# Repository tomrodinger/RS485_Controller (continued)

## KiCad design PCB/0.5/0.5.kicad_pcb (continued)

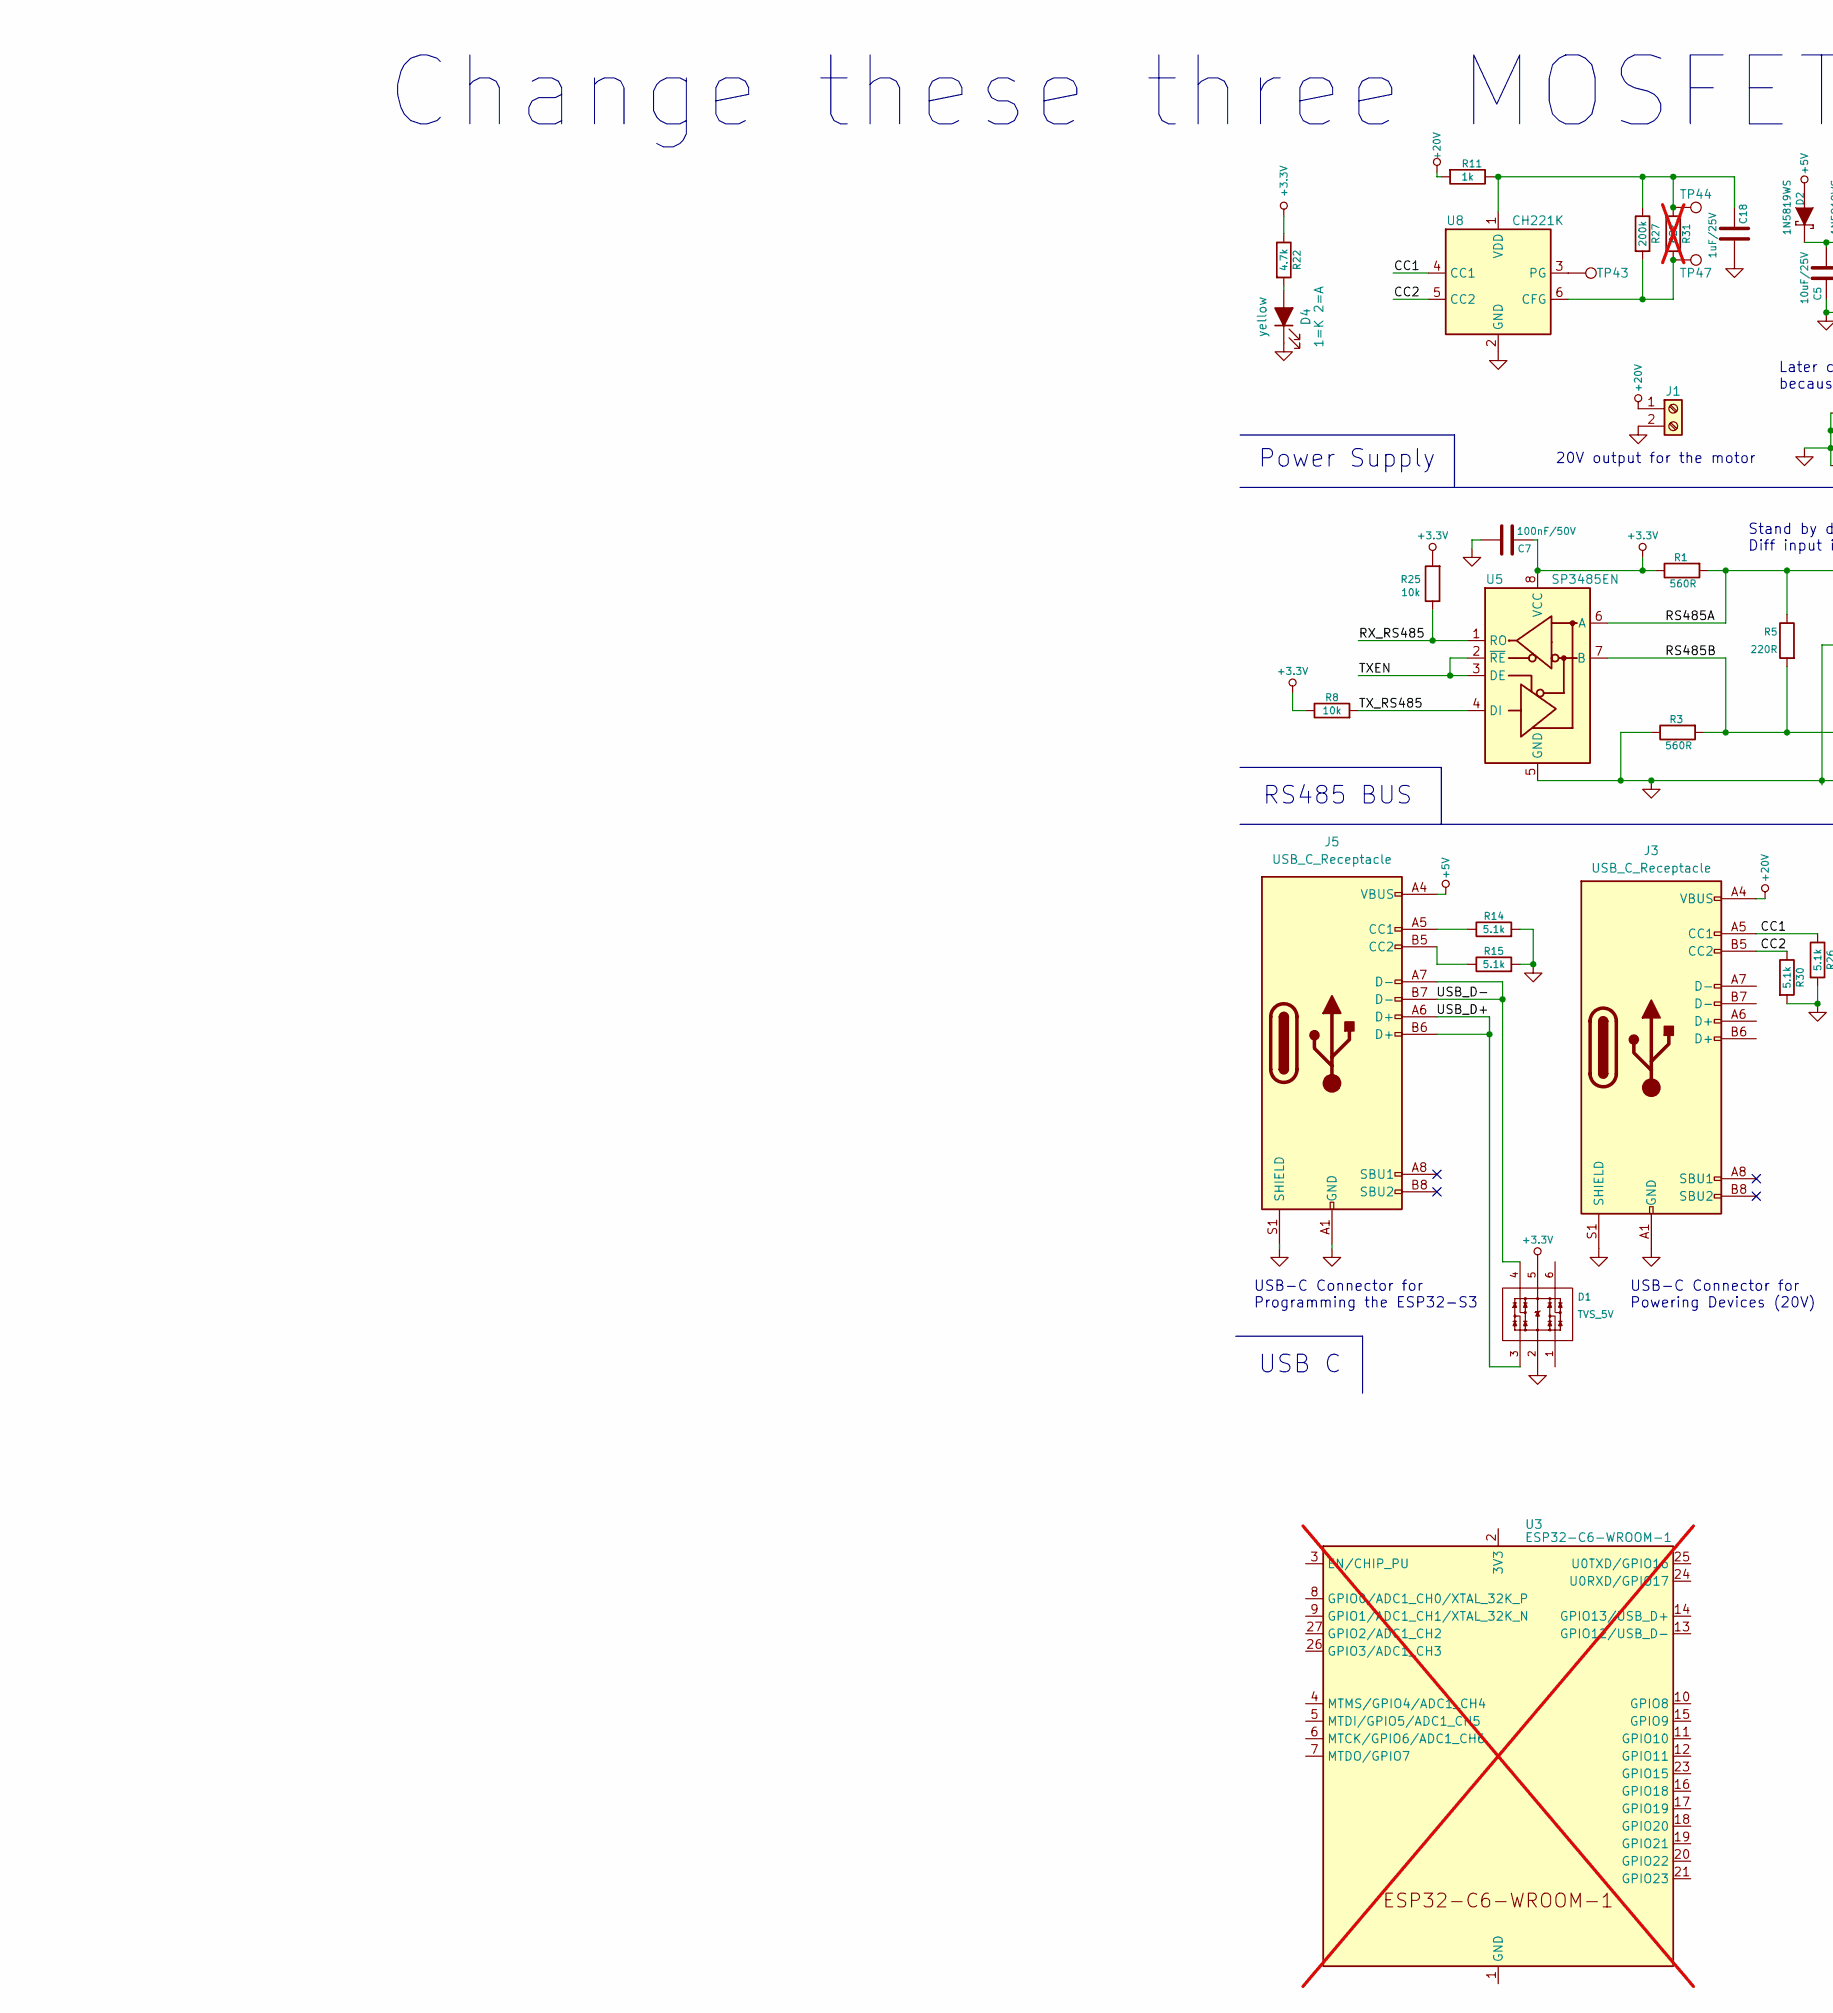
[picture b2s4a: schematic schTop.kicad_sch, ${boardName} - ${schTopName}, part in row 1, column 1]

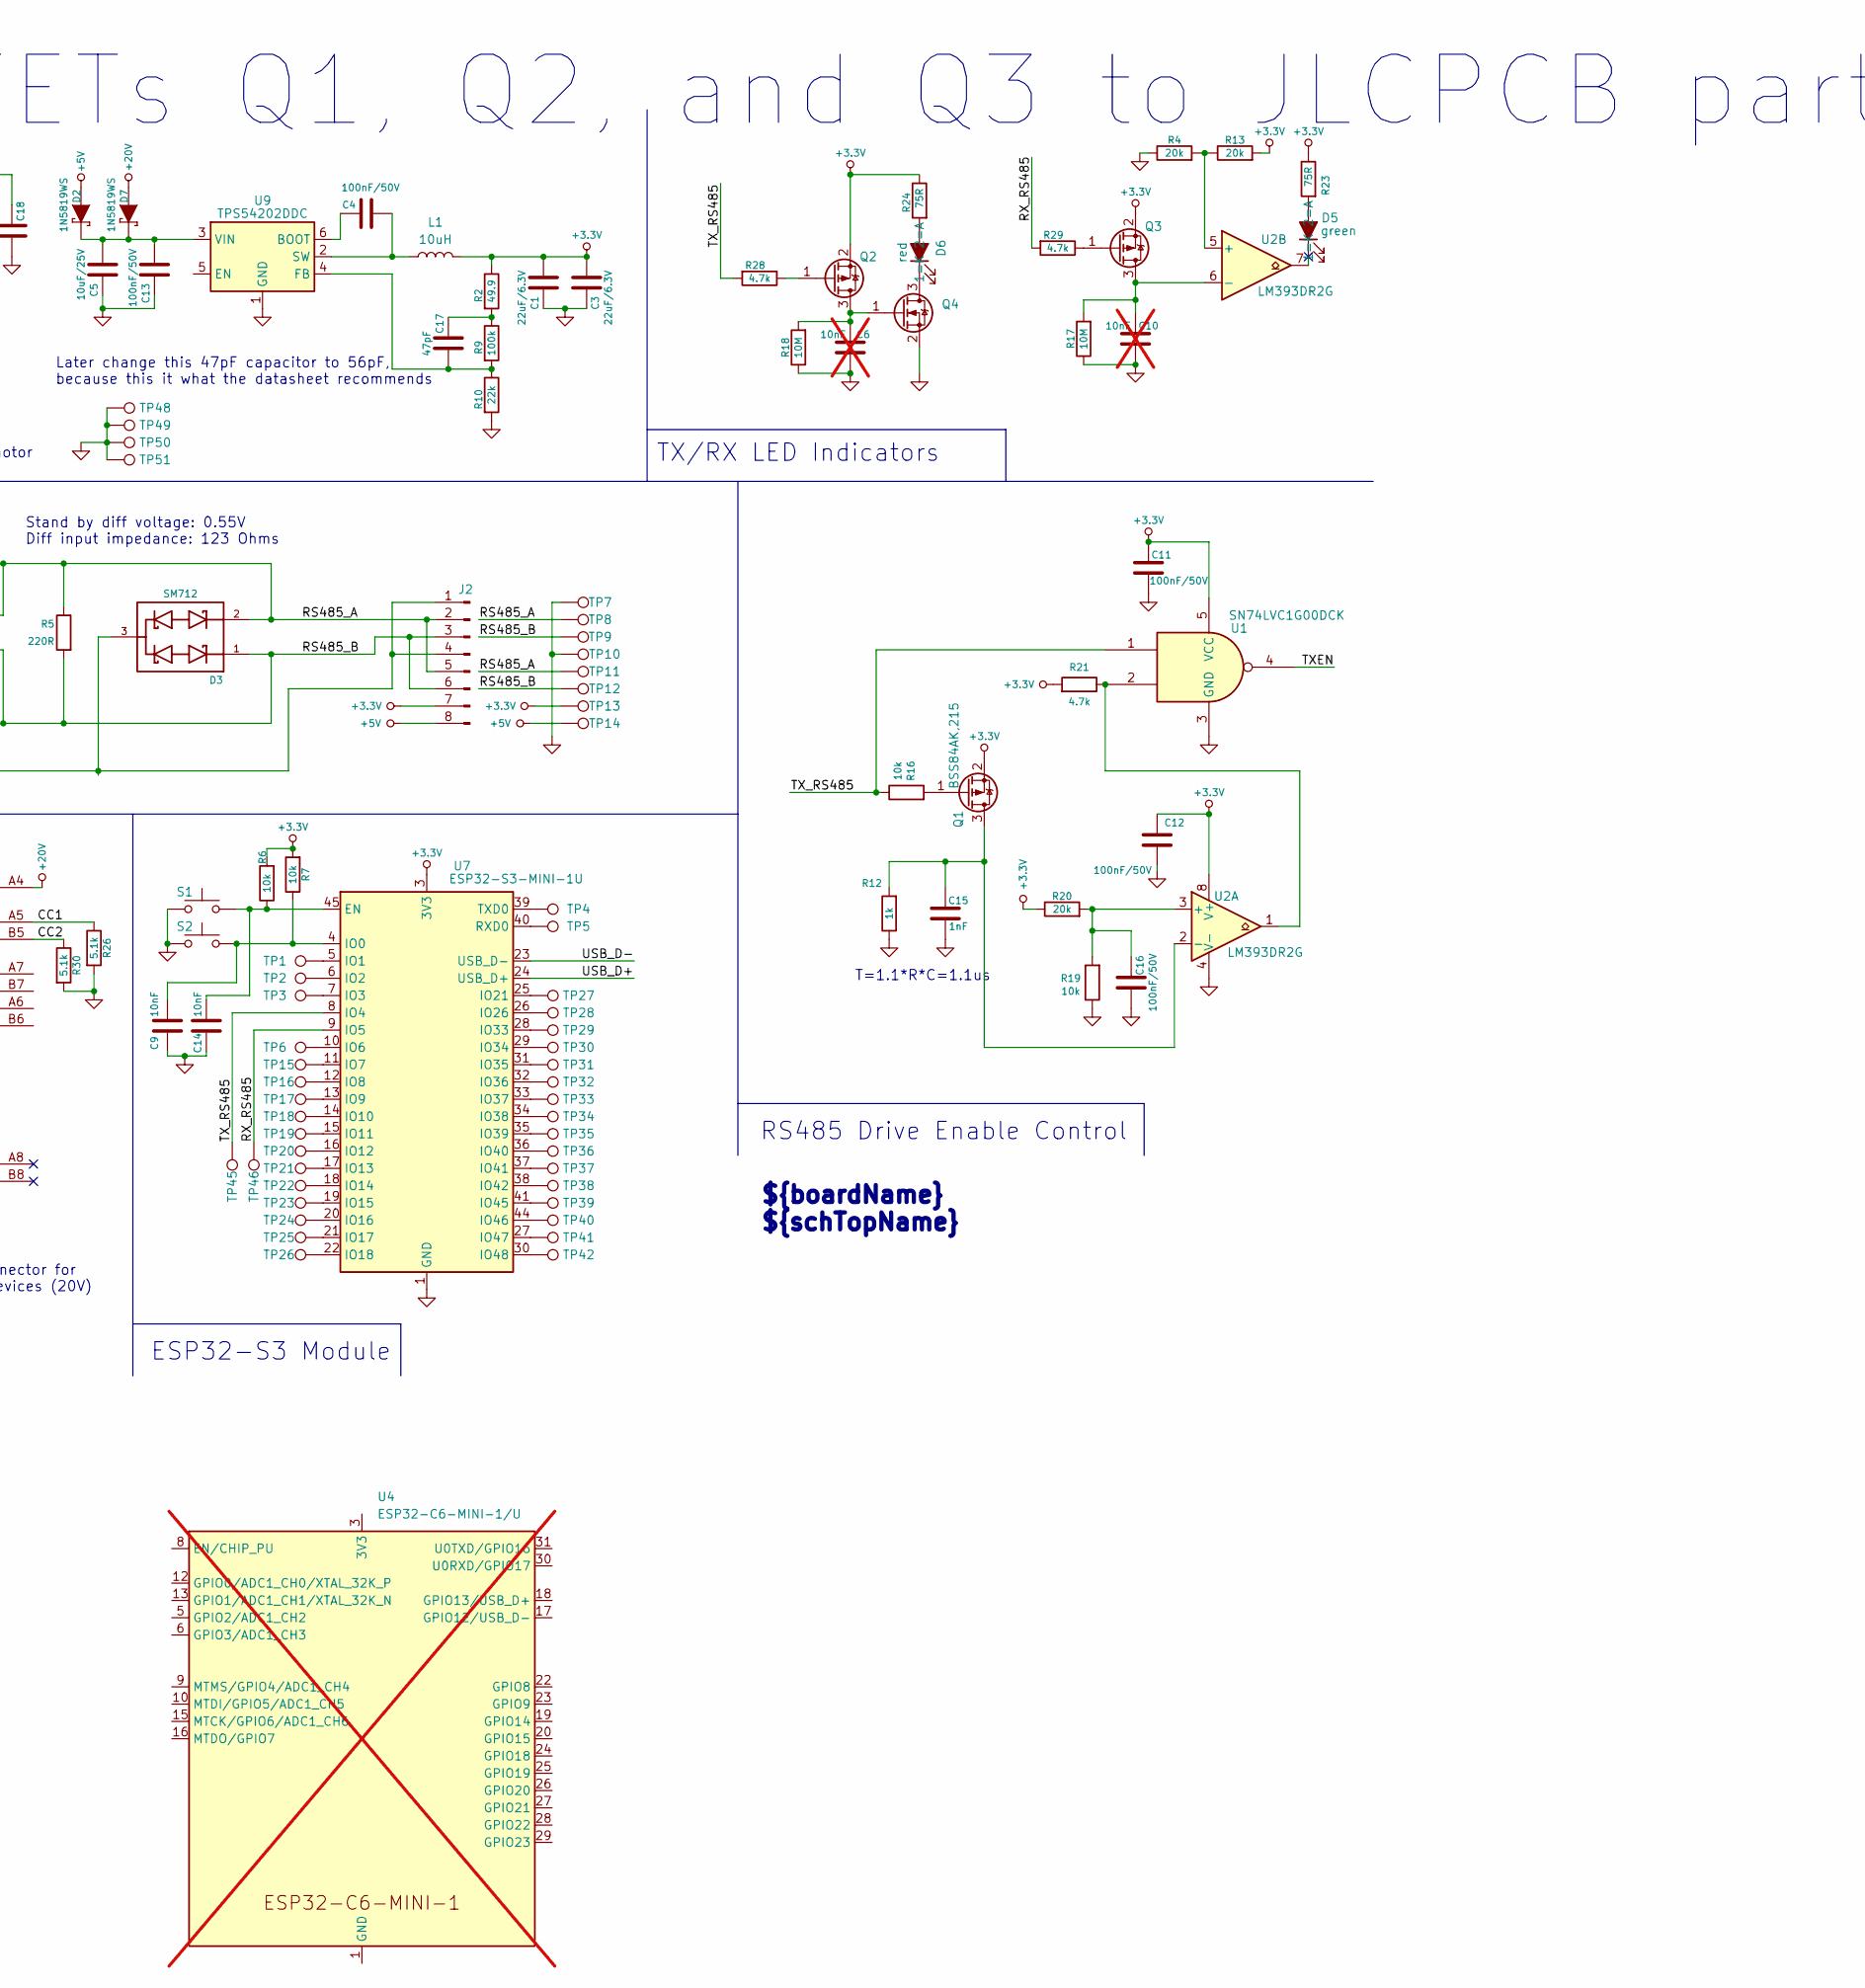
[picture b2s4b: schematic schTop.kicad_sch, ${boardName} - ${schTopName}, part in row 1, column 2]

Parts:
C1, C3: 22uF/6.3V; C_0603_1608Metric; Tolerance 10%; PartNumber CL10A106KP8NNNC; LCSC C59461
C4, C7, C11, C12, C13, C16: 100nF/50V; C_0603_1608Metric; Tolerance 10%; PartNumber CC0603KRX7R9BB104; Digikey 1276-6854-1-ND
C5: 10uF/25V; C_0603_1608Metric; LCSC C96446
C6: 10nF; C_0603_1608Metric; Tolerance 10%; PartNumber 0603B103K500NT; LCSC C57112; not fitted
C9, C14: 10nF; C_0603_1608Metric; LCSC C57112
C10: 10nF; C_0603_1608Metric; Tolerance 10%; PartNumber 0603B103K500NT; Digikey ---; not fitted
C15: 1nF; C_0603_1608Metric; Tolerance 10%; PartNumber CL10B102KB8NNNC; LCSC C1588
C17: 47pF; C_0603_1608Metric; LCSC C1671
C18: 1uF/25V; C_0603_1608Metric; LCSC C15849
D1: TVS_5V; SOT23-6L; Tolerance _; PartNumber TPIP4220CZ6; Digikey !1727-2751-1-ND
D2, D7: 1N5819WS; SOD323; LCSC C191023
D3: SM712; SOT23-3; Tolerance _; PartNumber SM712; Digikey !F6450CT-ND
D4: yellow; LED_0805_2012Metric; PartNumber KT-0805Y; LCSC C2296
D5: green; LED_0805_2012Metric; PartNumber KT-0805G; LCSC C2297
D6: red; LED_0805_2012Metric; PartNumber NCD0805R1; LCSC C84256
J1: Screw_Terminal_01x02; 2P_screw_terminal; LCSC C8404
J2: TSM-108-01-T-SH-A-P-TR; Connector_8-pin_SMT_hole_1.5mm; LCSC C9900147851
J3, J5: USB_C_Receptacle; USB_C_Receptacle_Palconn_UTC16-G; LCSC C2765186
L1: 10uH; Inductor_7.3x6.6mm; LCSC C128692
Q1, Q2, Q3: BSS84AK,215; SOT-23; Tolerance _; PartNumber BSS84AK,215; Digikey ---
Q4: Q_NMOS_GSD; SOT-23; Part Number 2N7002; LCSC C8545
R1, R3: 560R; R_0603_1608Metric; Tolerance 1%; PartNumber 0603WAF5600T5E; LCSC C23204
R2: 49.9; R_0603_1608Metric; LCSC C23185
R4, R13, R20: 20k; R_0603_1608Metric; Tolerance 1%; PartNumber 0603WAF2002T5E; LCSC C4184
R5: 220R; R_0603_1608Metric; Tolerance 5%; PartNumber 0603WAF2200T5E; LCSC C22962
R6, R7, R8, R16, R19, R25: 10k; R_0603_1608Metric; Tolerance 1%; PartNumber 0603WAF1002T5E; LCSC C25804
R9: 100k; R_0603_1608Metric; LCSC C25803
R10: 22k; R_0603_1608Metric; LCSC C31850
R11, R12: 1k; R_0603_1608Metric; Tolerance 1%; PartNumber 0603WAF1001T5E; Digikey 311-1.00KHRCT-ND
R14, R15, R26, R30: 5.1k; R_0402_1005Metric; Tolerance 1%; LCSC C25905
R17, R18: 10M; R_0603_1608Metric; PartNumber 0603WAF1005T5E; LCSC C7250
R21, R22, R28, R29: 4.7k; R_0603_1608Metric; Tolerance 1%; PartNumber 0603WAF4701T5E; LCSC C23162
R23, R24: 75R; R_0603_1608Metric; Tolerance 1%; PartNumber 0603WAF750JT5E; LCSC C4275
R27: 200k; R_0603_1608Metric; LCSC C25811
R31: 62k; R_0603_1608Metric; LCSC C23221; not fitted
S1, S2: SW_Push; button; LCSC C720477
TP1, TP2, TP3, TP4, TP5, TP6, TP15, TP16, TP17, TP18, TP19, TP20, TP21, TP22, TP23, TP24, TP25, TP26, TP27, TP28, TP29, TP30, TP31, TP32, TP33, TP34, TP35, TP36, TP37, TP38, TP39, TP40, TP41, TP42, TP43, TP44, TP45, TP46, TP47, TP48, TP49, TP50, TP51: TestPoint; testpoint_no_border
TP7, TP8, TP9, TP10, TP11, TP12, TP13, TP14: TestPoint; testpoint_no_border_surface_mount
U1: SN74LVC1G00DCK; Texas_R-PDSO-G5_DCK-5; LCSC C2976658
U2: LM393DR2G; SOIC-8_3.9x4.9mm_P1.27mm; Tolerance _; PartNumber LM393DR2G; Digikey _
U3: ESP32-C6-WROOM-1; not fitted
U4: ESP32-C6-MINI-1/U; ESP32-C6-MINI-1; not fitted
U5: SP3485EN; SOIC-8_3.9x4.9mm_P1.27mm; Tolerance _; PartNumber SP3485EN-L/TR; LCSC C8963
U7: ESP32-S3-MINI-1U; ESP32-S2-MINI-1U; LCSC C2980299
U8: CH221K; SOT-23-6; LCSC C5125736
U9: TPS54202DDC; SOT-23-6; LCSC C191884

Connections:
+3.3V: C1.1, C3.1, C7.2, C11.2, C12.2, D1.5 (VDD), J2.7, L1.2, Q1.2 (S), Q2.2 (S), Q3.2 (S), R1.1, R2.1, R6.2, R7.2, R8.1, R13.2, R20.1, R21.2, R22.1, R23.1, R24.1, R25.2, TP13.1, U1.5 (VCC), U2.8 (V+), U5.8 (VCC), U7.3 (3V3)
+5V: D2.1 (A), J2.8, J5.A4 (VBUS), J5.A9 (VBUS), J5.B4 (VBUS), J5.B9 (VBUS), TP14.1
+20V: D7.1 (A), J1.1, J3.A4 (VBUS), J3.A9 (VBUS), J3.B4 (VBUS), J3.B9 (VBUS), R11.2
/index/schTop/CC1: J3.A5 (CC1), R26.1, U8.4 (CC1)
/index/schTop/CC2: J3.B5 (CC2), R30.1, U8.5 (CC2)
/index/schTop/RS485A: D3.2 (cathode), J2.2, J2.5, R1.2, R5.1, TP8.1, TP11.1, U5.6 (A)
/index/schTop/RS485B: D3.1 (Anode), J2.3, J2.6, R3.2, R5.2, TP9.1, TP12.1, U5.7 (B)
/index/schTop/RX_RS485: R25.1, R29.2, TP46.1, U5.1 (RO), U7.9 (IO5)
/index/schTop/TXEN: U1.4, U5.2 (~RE), U5.3 (DE)
/index/schTop/TX_RS485: R8.2, R16.1, R28.2, TP45.1, U1.1, U5.4 (DI), U7.8 (IO4)
/index/schTop/USB_D+: D1.3 (IO2), J5.A6 (D+), J5.B6 (D+), U7.24 (USB_D+)
/index/schTop/USB_D-: D1.4 (IO3), J5.A7 (D-), J5.B7 (D-), U7.23 (USB_D-)
GND: C1.2, C3.2, C5.2, C6.1, C7.1, C9.1, C10.1, C11.1, C12.1, C13.2, C14.1, C15.1, C16.1, C18.2, D1.2 (GND), D3.3 (AK), D4.1 (K), J1.2, J2.1, J2.4, J3.A1 (GND), J3.A12 (GND), J3.B1 (GND), J3.B12 (GND), J3.S1 (SHIELD), J5.A1 (GND), J5.A12 (GND), J5.B1 (GND), J5.B12 (GND), J5.S1 (SHIELD), Q4.2 (S), R3.1, R4.1, R10.2, R12.1, R14.2, R15.2, R17.1, R18.1, R19.1, R26.2, R30.2, S1.1, S2.1, TP7.1, TP10.1, TP48.1, TP49.1, TP50.1, TP51.1, U1.3 (GND), U2.4 (V-), U5.5 (GND), U7.1 (GND), U7.2 (GND), U7.42 (GND), U7.43 (GND), U7.46 (GND), U7.47 (GND), U7.48 (GND), U7.49 (GND), U7.50 (GND), U7.51 (GND), U7.52 (GND), U7.53 (GND), U7.54 (GND), U7.55 (GND), U7.56 (GND), U7.57 (GND), U7.58 (GND), U7.59 (GND), U7.60 (GND), U7.61 (GND), U7.62 (GND), U7.63 (GND), U7.64 (GND), U7.65 (GND), U8.2 (GND), U9.1 (GND)
unnamed: C17.1, R2.2, R9.1
unnamed: C5.1, C13.1, D2.2 (K), D7.2 (K), U9.3 (VIN)
unnamed: D4.2 (A), R22.2
unnamed: D5.2 (A), R23.2
unnamed: D6.2 (A), R24.2
unnamed: D6.1 (K), Q4.3 (D)
unnamed: J5.A5 (CC1), R14.1
unnamed: J5.B5 (CC2), R15.1
unnamed: C15.2, Q1.3 (D), R12.2, U2.2 (-)
unnamed: Q1.1 (G), R16.2
unnamed: C6.2, Q2.3 (D), Q4.1 (G), R18.2
unnamed: Q2.1 (G), R28.1
unnamed: C10.2, Q3.3 (D), R17.2, U2.6 (-)
unnamed: Q3.1 (G), R29.1
unnamed: R21.1, U1.2, U2.1
unnamed: C16.2, R19.2, R20.2, U2.3 (+)
unnamed: R4.2, R13.1, U2.5 (+)
unnamed: U3.1 (GND), U3.28 (GND), U3.29 (GND)
unnamed: U4.1 (GND), U4.2 (GND), U4.11 (GND), U4.14 (GND), U4.36 (GND), U4.37 (GND), U4.38 (GND), U4.39 (GND), U4.40 (GND), U4.41 (GND), U4.42 (GND), U4.43 (GND), U4.44 (GND), U4.45 (GND), U4.46 (GND), U4.47 (GND), U4.48 (GND), U4.49 (GND), U4.50 (GND), U4.51 (GND), U4.52 (GND), U4.53 (GND)
unnamed: C14.2, R6.1, S1.2, U7.45 (EN)
unnamed: C9.2, R7.1, S2.2, U7.4 (IO0)
unnamed: TP1.1, U7.5 (IO1)
unnamed: TP2.1, U7.6 (IO2)
unnamed: TP3.1, U7.7 (IO3)
unnamed: TP6.1, U7.10 (IO6)
unnamed: TP15.1, U7.11 (IO7)
unnamed: TP16.1, U7.12 (IO8)
unnamed: TP17.1, U7.13 (IO9)
unnamed: TP18.1, U7.14 (IO10)
unnamed: TP19.1, U7.15 (IO11)
unnamed: TP20.1, U7.16 (IO12)
unnamed: TP21.1, U7.17 (IO13)
unnamed: TP22.1, U7.18 (IO14)
unnamed: TP23.1, U7.19 (IO15)
unnamed: TP24.1, U7.20 (IO16)
unnamed: TP25.1, U7.21 (IO17)
unnamed: TP26.1, U7.22 (IO18)
unnamed: TP27.1, U7.25 (IO21)
unnamed: TP28.1, U7.26 (IO26)
unnamed: TP29.1, U7.28 (IO33)
unnamed: TP30.1, U7.29 (IO34)
unnamed: TP31.1, U7.31 (IO35)
unnamed: TP32.1, U7.32 (IO36)
unnamed: TP33.1, U7.33 (IO37)
unnamed: TP34.1, U7.34 (IO38)
unnamed: TP35.1, U7.35 (IO39)
unnamed: TP36.1, U7.36 (IO40)
unnamed: TP37.1, U7.37 (IO41)
unnamed: TP38.1, U7.38 (IO42)
unnamed: TP39.1, U7.41 (IO45)
unnamed: TP40.1, U7.44 (IO46)
unnamed: TP41.1, U7.27 (IO47)
unnamed: TP42.1, U7.30 (IO48)
unnamed: TP5.1, U7.40 (RXD0)
unnamed: TP4.1, U7.39 (TXD0)
unnamed: R27.2, R31.2, TP47.1, U8.6 (CFG)
unnamed: TP43.1, U8.3 (PG)
unnamed: C18.1, R11.1, R27.1, R31.1, TP44.1, U8.1 (VDD)
unnamed: C4.2, U9.6 (BOOT)
unnamed: C17.2, R9.2, R10.1, U9.4 (FB)
unnamed: C4.1, L1.1, U9.2 (SW)

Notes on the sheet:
Stand by diff voltage: 0.55V Diff input impedance: 123 Ohms
Later change this 47pF capacitor to 56pF, because this it what the datasheet recommends
RS485 BUS
T=1.1*R*C=1.1us
20V output for the motor
Change these three MOSFETs Q1, Q2, and Q3 to JLCPCB part C5337191 to save cost.
TX/RX LED Indicators
USB C
Power Supply
USB-C Connector for Programming the ESP32-S3
RS485 Drive Enable Control
USB-C Connector for Powering Devices (20V)
${boardName} ${schTopName}
ESP32-S3 Module

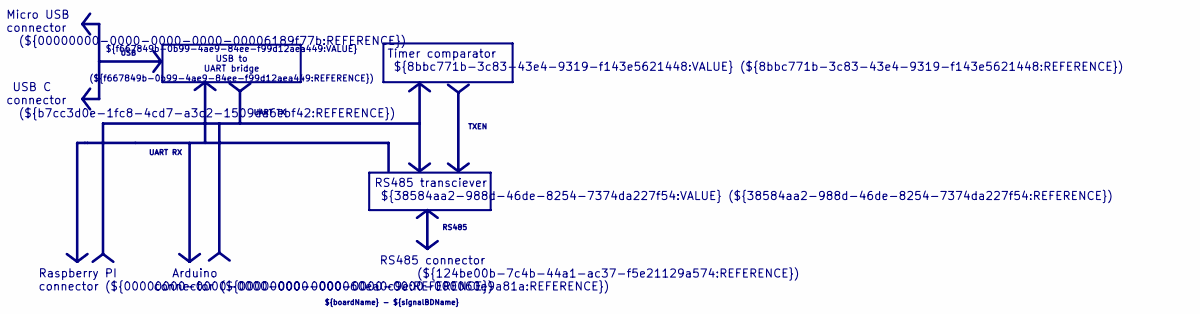
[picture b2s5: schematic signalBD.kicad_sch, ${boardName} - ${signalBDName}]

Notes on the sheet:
RS485 transciever ${38584aa2-988d-46de-8254-7374da227f54:VALUE} (${38584aa2-988d-46de-8254-7374da227f54:REFERENCE})
${boardName} - ${signalBDName}
RS485 connector (${124be00b-7c4b-44a1-ac37-f5e21129a574:REFERENCE})
Raspberry PI connector (${00000000-0000-0000-0000-000060ea0c9e:REFERENCE})
UART TX
USB C connector (${b7cc3d0e-1fc8-4cd7-a3c2-1509da6ebf42:REFERENCE})
UART RX
RS485
TXEN
USB
Timer comparator ${8bbc771b-3c83-43e4-9319-f143e5621448:VALUE} (${8bbc771b-3c83-43e4-9319-f143e5621448:REFERENCE})
Arduino connector (${00000000-0000-0000-0000-000060e9a81a:REFERENCE})
Micro USB connector (${00000000-0000-0000-0000-00006189f77b:REFERENCE})
${f667849b-0b99-4ae9-84ee-f99d12aea449:VALUE} USB to UART bridge (${f667849b-0b99-4ae9-84ee-f99d12aea449:REFERENCE})

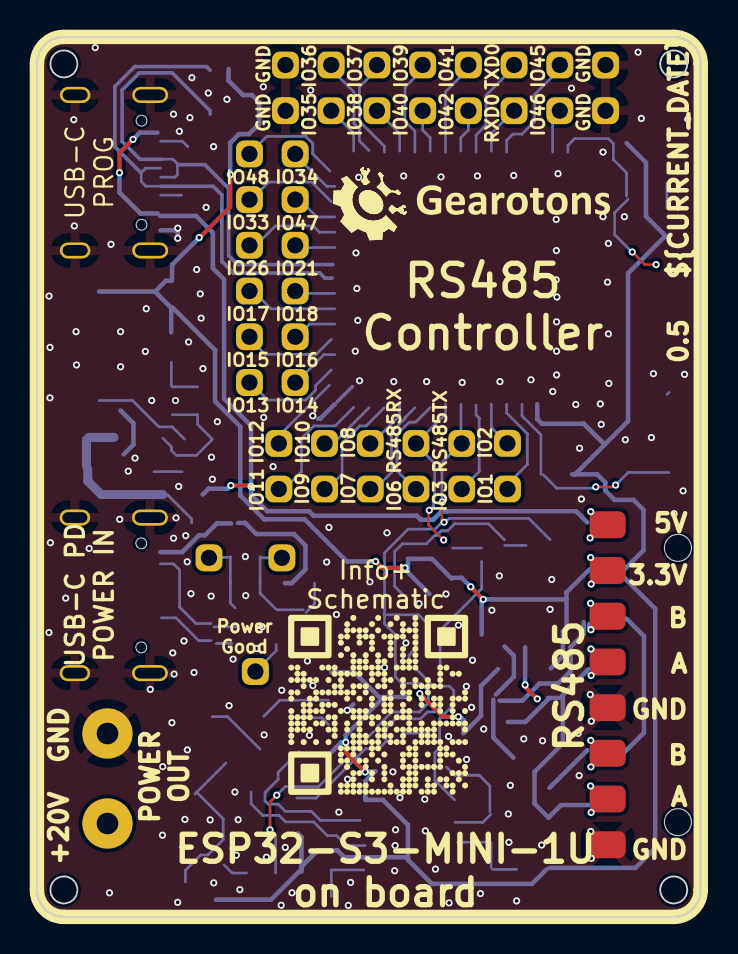
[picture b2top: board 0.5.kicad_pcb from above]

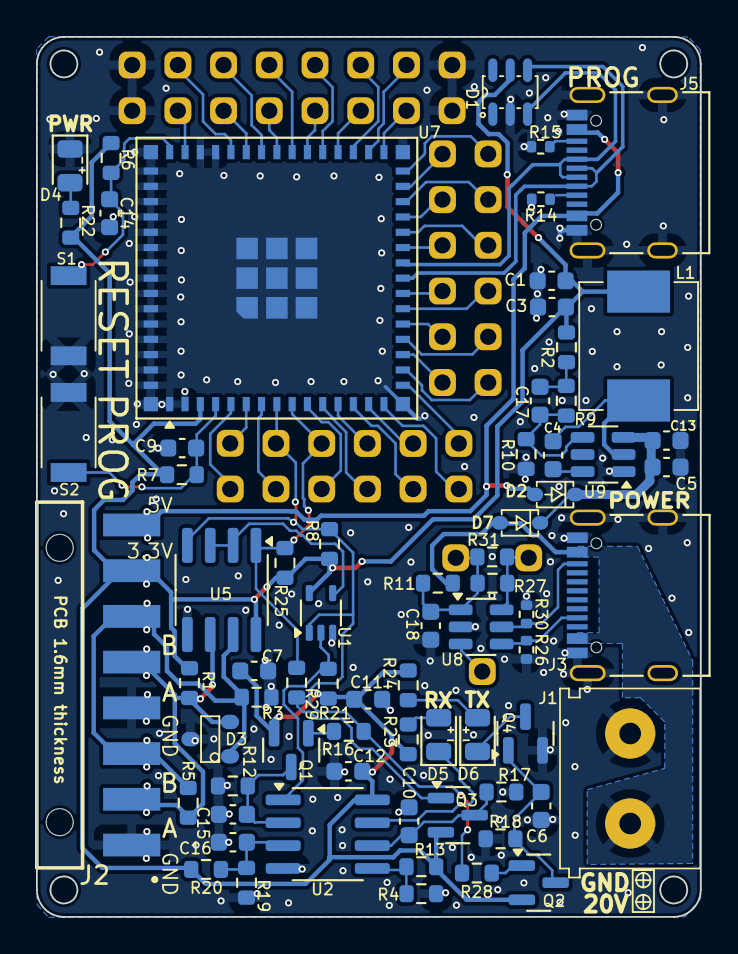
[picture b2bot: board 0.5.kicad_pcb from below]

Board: 2 copper layers, 36.9 x 48.9 mm, 122 parts (108 on the bottom side), 72 nets.

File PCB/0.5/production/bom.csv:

Designator,Footprint,Quantity,Value,LCSC Part #
"C1, C3",0603,2,22uF/6.3V,C59461
"C11, C12, C13, C16, C4, C7",0603,6,100nF/50V,C14663
"C14, C9",0603,2,10nF,C57112
C15,0603,1,1nF,C1588
C17,0603,1,47pF,C1671
C18,0603,1,1uF/25V,C15849
C5,0603,1,10uF/25V,C96446
D1,SOT23-6L,1,TVS_5V,C558417
"D2, D7",SOD323,2,1N5819WS,C191023
D3,SOT23-3,1,SM712,C293966
D4,0805,1,yellow,C2296
D5,0805,1,green,C2297
D6,0805,1,red,C84256
J1,2P_screw_terminal,1,Screw_Terminal_01x02,C8404
J2,Connector_8-pin_SMT_hole_1.5mm,1,TSM-108-01-T-SH-A-P-TR,C9900147851
"J3, J5",USB_C_Receptacle_Palconn_UTC16-G,2,USB_C_Receptacle,C2765186
L1,Inductor_7.3x6.6mm,1,10uH,C128692
"Q1, Q2, Q3",SOT-23,3,"BSS84AK,215",C127273
Q4,SOT-23,1,Q_NMOS_GSD, C8545
"R1, R3",0603,2,560R,C23204
R10,0603,1,22k,C31850
"R11, R12",0603,2,1k,C21190
"R13, R20, R4",0603,3,20k,C4184
"R14, R15, R26, R30",0402,4,5.1k,C25905
"R16, R19, R25, R6, R7, R8",0603,6,10k,C25804
"R17, R18",0603,2,10M,C7250
R2,0603,1,49.9,C23185
"R21, R22, R28, R29",0603,4,4.7k,C23162
"R23, R24",0603,2,75R,C4275
R27,0603,1,200k,C25811
R5,0603,1,220R,C22962
R9,0603,1,100k,C25803
"S1, S2",button,2,SW_Push,C720477
U1,Texas_R-PDSO-G5_DCK-5,1,SN74LVC1G00DCK,C2976658
U2,SOIC-8_3.9x4.9mm_P1.27mm,1,LM393DR2G,C7955
U5,SOIC-8_3.9x4.9mm_P1.27mm,1,SP3485EN,C8963
U7,ESP32-S2-MINI-1U,1,ESP32-S3-MINI-1U,C2980299
U8,SOT-23-6,1,CH221K,C5125736
U9,SOT-23-6,1,TPS54202DDC,C191884

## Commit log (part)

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2025-10-18 !!! CRITICAL ISSUE: D1, the 5V TVS that protects the USB lines must be removed before use. Otherwise if you connect USB-C power, and 20V is supplied, it will burn this chip and probably damage the US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
2025-11-23 Adding version 0.2 This adds a second USB-C connector Cleans up the board to make is clean looking Adds QR code Adds holes in the corners Fixes problem with 20V going to the TVS protection in the USB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
